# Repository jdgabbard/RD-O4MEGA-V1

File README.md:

# RD-O4MEGA-V1
 4MB Memory for Omega Home Computer

This is a memory module for the Omega Home Computer designed to better fit the printable cases available.  And should be considered a fork of: https://github.com/capsule5000/O4MEGA_v2

While Jordi did a good job on the design, it's just too large for the printable cases in my experience.  And because of this, I have redesigned the board using SMD components.  That said, this board should support either HM628512 or AS6C4008 SRAMs.  When matched with standard height male and female headers this provides ample clearance for socketed ICs.

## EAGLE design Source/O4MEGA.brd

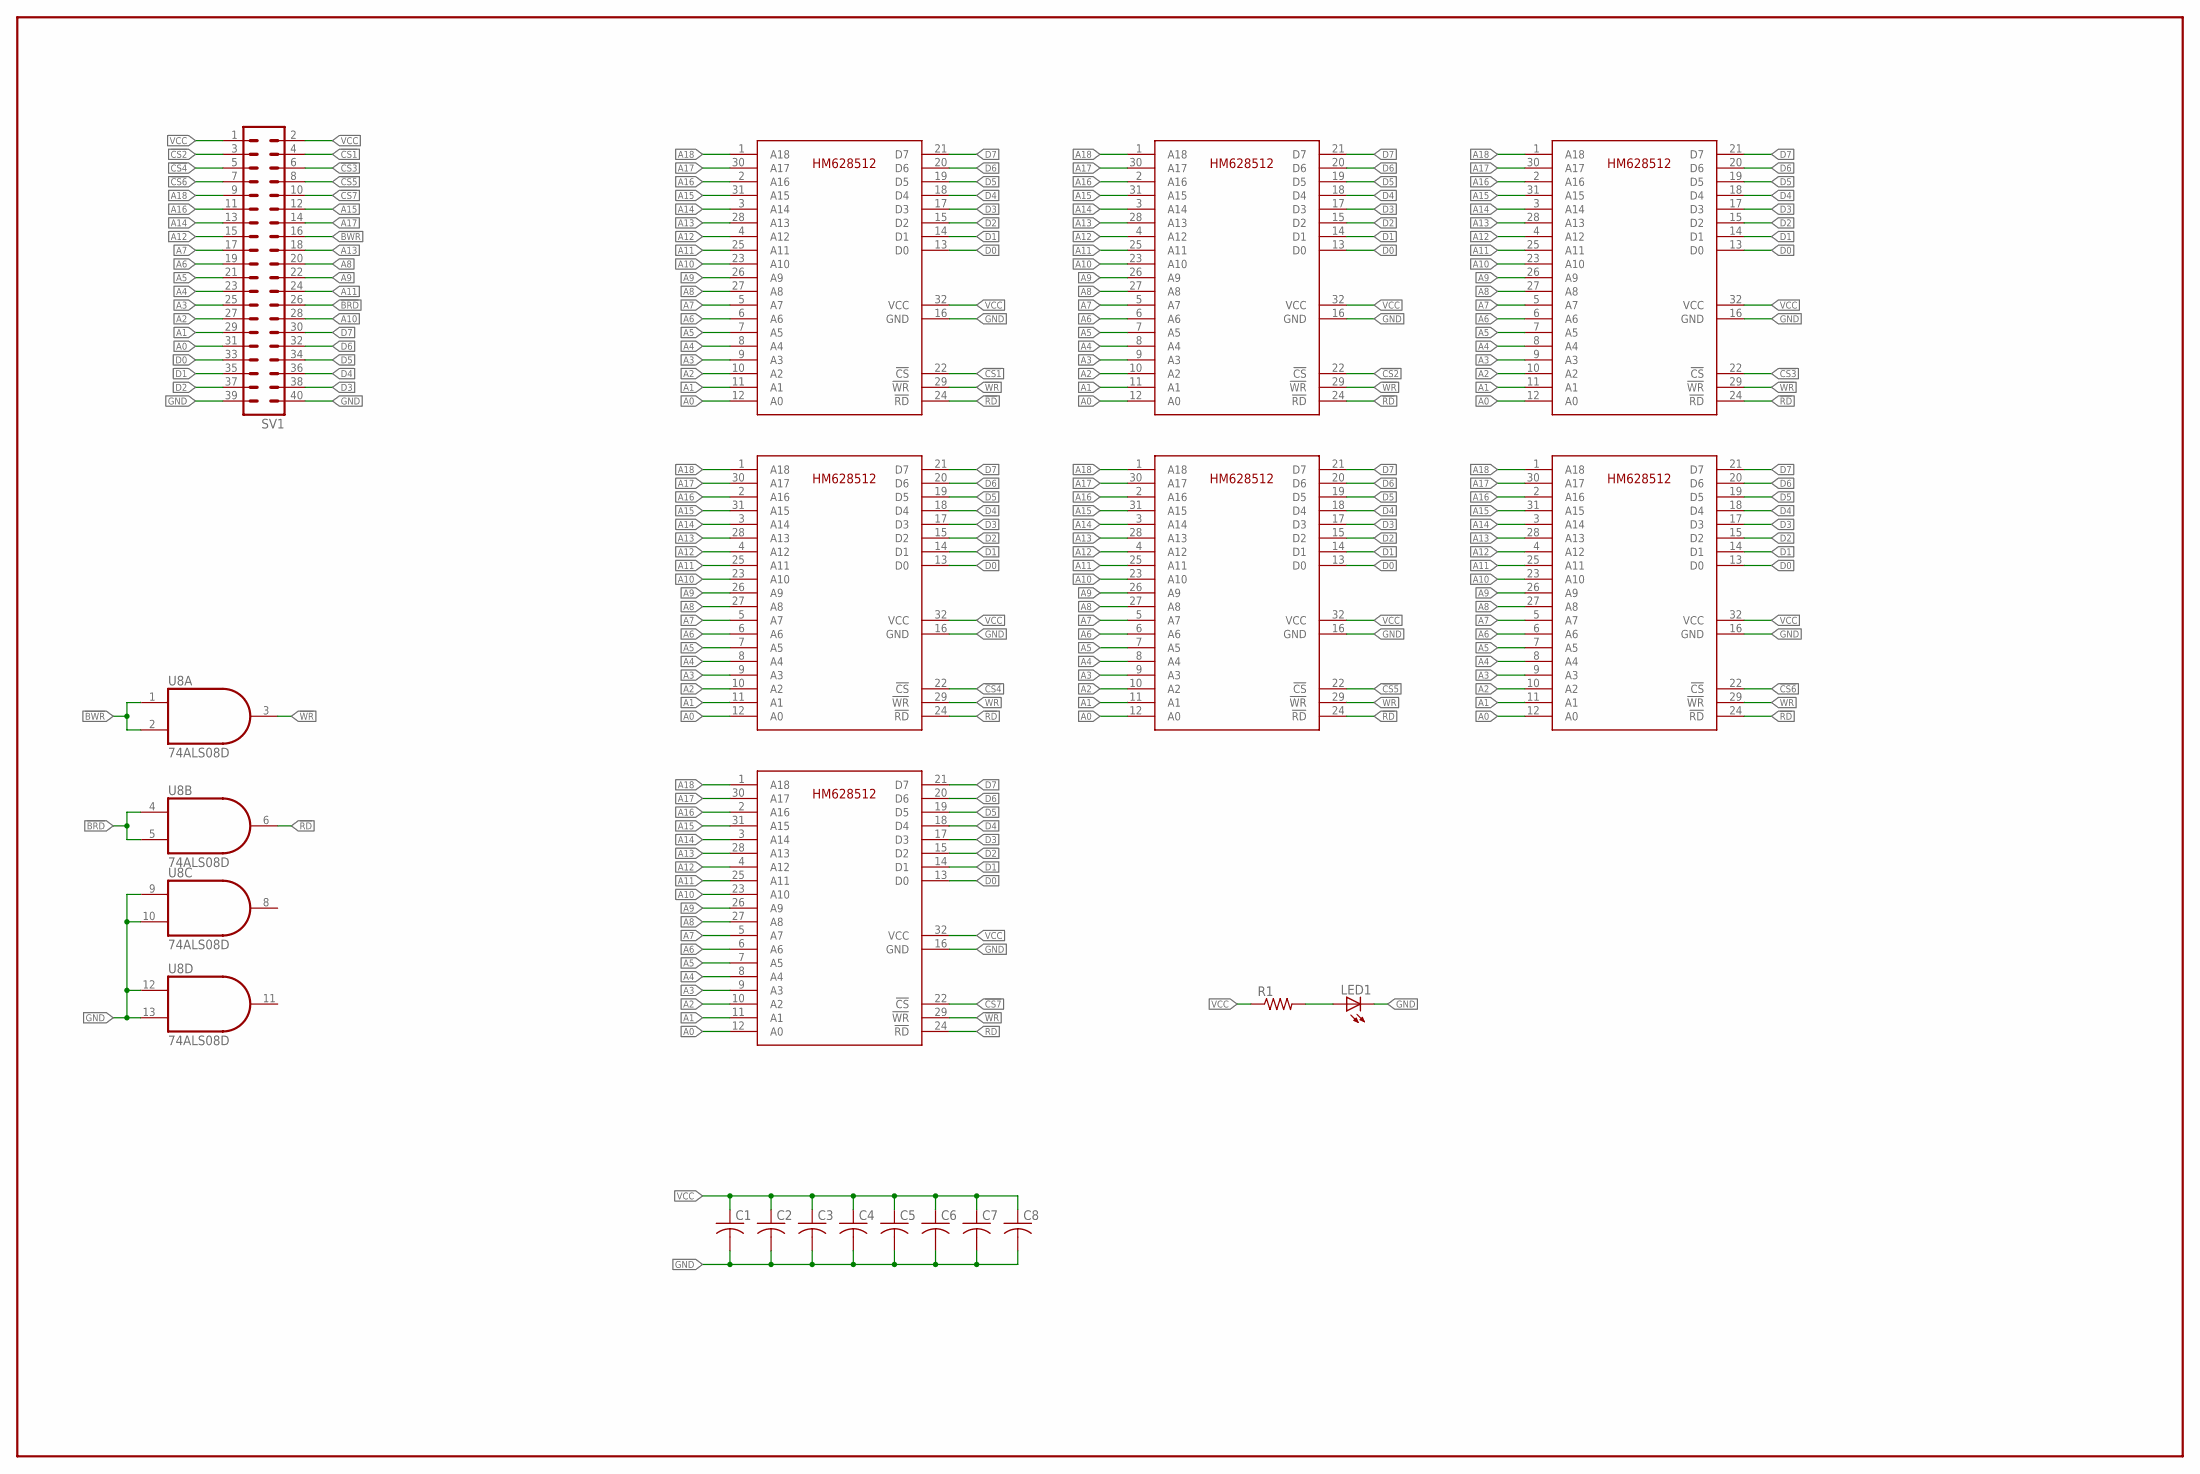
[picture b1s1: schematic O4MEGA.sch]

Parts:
C1, C2, C3, C4, C5, C6, C7, C8: C-USC0805K; C0805K
LED1: LEDCHIP-LED0805; CHIP-LED0805
R1: R-US_M0805; M0805
SV1: MA20-2
U1, U2, U3, U4, U5, U6, U7: HM628512; SOP32L
U8: 74ALS08D; SO14

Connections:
!BRD: SV1.26, U8.4 (I0), U8.5 (I1)
!BWR: SV1.16, U8.1 (I0), U8.2 (I1)
!CS1: SV1.4, U1.22 (!CS)
!CS2: SV1.3, U2.22 (!CS)
!CS3: SV1.6, U3.22 (!CS)
!CS4: SV1.5, U4.22 (!CS)
!CS5: SV1.8, U5.22 (!CS)
!CS6: SV1.7, U6.22 (!CS)
!CS7: SV1.10, U7.22 (!CS)
!RD: U1.24 (!RD), U2.24 (!RD), U3.24 (!RD), U4.24 (!RD), U5.24 (!RD), U6.24 (!RD), U7.24 (!RD), U8.6 (O)
!WR: U1.29 (!WR), U2.29 (!WR), U3.29 (!WR), U4.29 (!WR), U5.29 (!WR), U6.29 (!WR), U7.29 (!WR), U8.3 (O)
A0: SV1.31, U1.12 (A0), U2.12 (A0), U3.12 (A0), U4.12 (A0), U5.12 (A0), U6.12 (A0), U7.12 (A0)
A1: SV1.29, U1.11 (A1), U2.11 (A1), U3.11 (A1), U4.11 (A1), U5.11 (A1), U6.11 (A1), U7.11 (A1)
A2: SV1.27, U1.10 (A2), U2.10 (A2), U3.10 (A2), U4.10 (A2), U5.10 (A2), U6.10 (A2), U7.10 (A2)
A3: SV1.25, U1.9 (A3), U2.9 (A3), U3.9 (A3), U4.9 (A3), U5.9 (A3), U6.9 (A3), U7.9 (A3)
A4: SV1.23, U1.8 (A4), U2.8 (A4), U3.8 (A4), U4.8 (A4), U5.8 (A4), U6.8 (A4), U7.8 (A4)
A5: SV1.21, U1.7 (A5), U2.7 (A5), U3.7 (A5), U4.7 (A5), U5.7 (A5), U6.7 (A5), U7.7 (A5)
A6: SV1.19, U1.6 (A6), U2.6 (A6), U3.6 (A6), U4.6 (A6), U5.6 (A6), U6.6 (A6), U7.6 (A6)
A7: SV1.17, U1.5 (A7), U2.5 (A7), U3.5 (A7), U4.5 (A7), U5.5 (A7), U6.5 (A7), U7.5 (A7)
A8: SV1.20, U1.27 (A8), U2.27 (A8), U3.27 (A8), U4.27 (A8), U5.27 (A8), U6.27 (A8), U7.27 (A8)
A9: SV1.22, U1.26 (A9), U2.26 (A9), U3.26 (A9), U4.26 (A9), U5.26 (A9), U6.26 (A9), U7.26 (A9)
A10: SV1.28, U1.23 (A10), U2.23 (A10), U3.23 (A10), U4.23 (A10), U5.23 (A10), U6.23 (A10), U7.23 (A10)
A11: SV1.24, U1.25 (A11), U2.25 (A11), U3.25 (A11), U4.25 (A11), U5.25 (A11), U6.25 (A11), U7.25 (A11)
A12: SV1.15, U1.4 (A12), U2.4 (A12), U3.4 (A12), U4.4 (A12), U5.4 (A12), U6.4 (A12), U7.4 (A12)
A13: SV1.18, U1.28 (A13), U2.28 (A13), U3.28 (A13), U4.28 (A13), U5.28 (A13), U6.28 (A13), U7.28 (A13)
A14: SV1.13, U1.3 (A14), U2.3 (A14), U3.3 (A14), U4.3 (A14), U5.3 (A14), U6.3 (A14), U7.3 (A14)
A15: SV1.12, U1.31 (A15), U2.31 (A15), U3.31 (A15), U4.31 (A15), U5.31 (A15), U6.31 (A15), U7.31 (A15)
A16: SV1.11, U1.2 (A16), U2.2 (A16), U3.2 (A16), U4.2 (A16), U5.2 (A16), U6.2 (A16), U7.2 (A16)
A17: SV1.14, U1.30 (A17), U2.30 (A17), U3.30 (A17), U4.30 (A17), U5.30 (A17), U6.30 (A17), U7.30 (A17)
A18: SV1.9, U1.1 (A18), U2.1 (A18), U3.1 (A18), U4.1 (A18), U5.1 (A18), U6.1 (A18), U7.1 (A18)
D0: SV1.33, U1.13 (D0), U2.13 (D0), U3.13 (D0), U4.13 (D0), U5.13 (D0), U6.13 (D0), U7.13 (D0)
D1: SV1.35, U1.14 (D1), U2.14 (D1), U3.14 (D1), U4.14 (D1), U5.14 (D1), U6.14 (D1), U7.14 (D1)
D2: SV1.37, U1.15 (D2), U2.15 (D2), U3.15 (D2), U4.15 (D2), U5.15 (D2), U6.15 (D2), U7.15 (D2)
D3: SV1.38, U1.17 (D3), U2.17 (D3), U3.17 (D3), U4.17 (D3), U5.17 (D3), U6.17 (D3), U7.17 (D3)
D4: SV1.36, U1.18 (D4), U2.18 (D4), U3.18 (D4), U4.18 (D4), U5.18 (D4), U6.18 (D4), U7.18 (D4)
D5: SV1.34, U1.19 (D5), U2.19 (D5), U3.19 (D5), U4.19 (D5), U5.19 (D5), U6.19 (D5), U7.19 (D5)
D6: SV1.32, U1.20 (D6), U2.20 (D6), U3.20 (D6), U4.20 (D6), U5.20 (D6), U6.20 (D6), U7.20 (D6)
D7: SV1.30, U1.21 (D7), U2.21 (D7), U3.21 (D7), U4.21 (D7), U5.21 (D7), U6.21 (D7), U7.21 (D7)
GND: C1.2, C2.2, C3.2, C4.2, C5.2, C6.2, C7.2, C8.2, LED1.C, SV1.39, SV1.40, U1.16 (GND), U2.16 (GND), U3.16 (GND), U4.16 (GND), U5.16 (GND), U6.16 (GND), U7.16 (GND), U8.7 (GND), U8.9 (I0), U8.10 (I1), U8.12 (I0), U8.13 (I1)
unnamed: LED1.A, R1.2
VCC: C1.1, C2.1, C3.1, C4.1, C5.1, C6.1, C7.1, C8.1, R1.1, SV1.1, SV1.2, U1.32 (VCC), U2.32 (VCC), U3.32 (VCC), U4.32 (VCC), U5.32 (VCC), U6.32 (VCC), U7.32 (VCC), U8.14 (VCC)

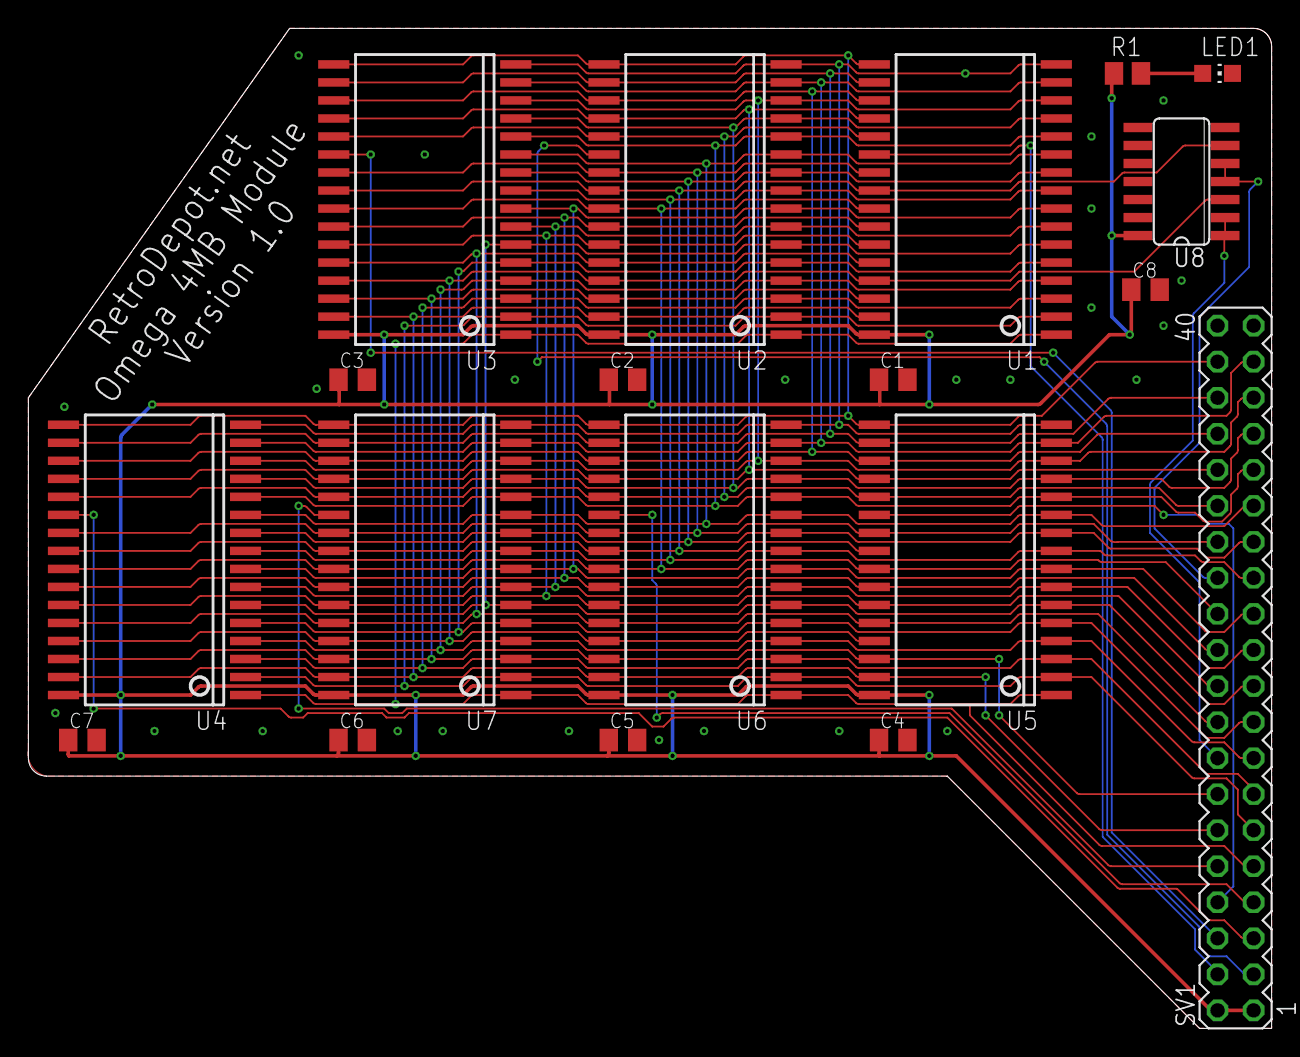
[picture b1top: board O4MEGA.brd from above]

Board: 2 copper layers, 87.6 x 70.5 mm, 19 parts (0 on the bottom side), 41 nets.
